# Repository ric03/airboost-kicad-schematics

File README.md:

# Airboost KiCad Schematics

Schematics for the airboost project. Powered by https://www.kicad.org/

## Commiting

Make sure to close KiCad before commiting. Otherwise temporary files are commited.

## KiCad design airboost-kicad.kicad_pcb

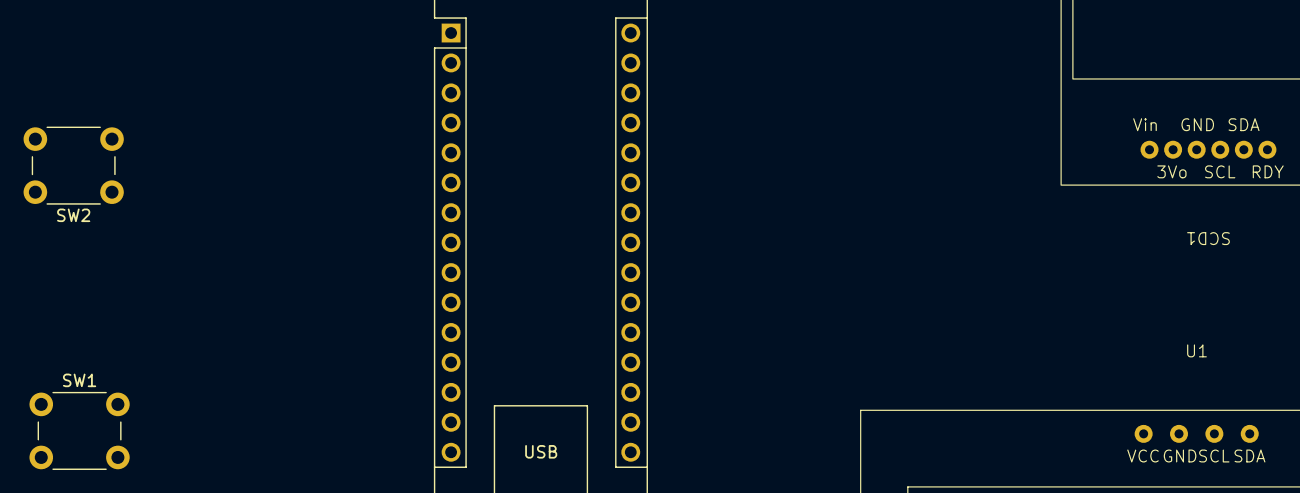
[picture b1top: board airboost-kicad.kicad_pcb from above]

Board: 2 copper layers, 5 parts (0 on the bottom side), 6 nets, no tracks yet.

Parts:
A1: Arduino_Nano_v2.x; Arduino_Nano
SCD1: Adafruit SCD30
SW1, SW2: SW_Push; SW_PUSH_6mm
U1: Display OLED; Mounted OLED Display

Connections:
/I2C.SCL: A1.24 (A5), SCD1.4 (SCL), U1.3 (SCL)
/I2C.SDA: A1.23 (A4), SCD1.5 (SDA), U1.4 (SDA)
GND: A1.4 (GND), SCD1.3 (GND), SW1.1, SW2.1, U1.2 (GND)
unnamed: A1.27 (+5V), SCD1.1 (Vin), U1.1 (VCC)
unnamed: A1.5 (D2), SW1.2
unnamed: A1.6 (D3), SW2.2

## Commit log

2024-05-26 docs: add schematics.png
2024-05-31 docs: add schematics.pdf
2024-05-31 fix: reposition resistor for bicolor led
